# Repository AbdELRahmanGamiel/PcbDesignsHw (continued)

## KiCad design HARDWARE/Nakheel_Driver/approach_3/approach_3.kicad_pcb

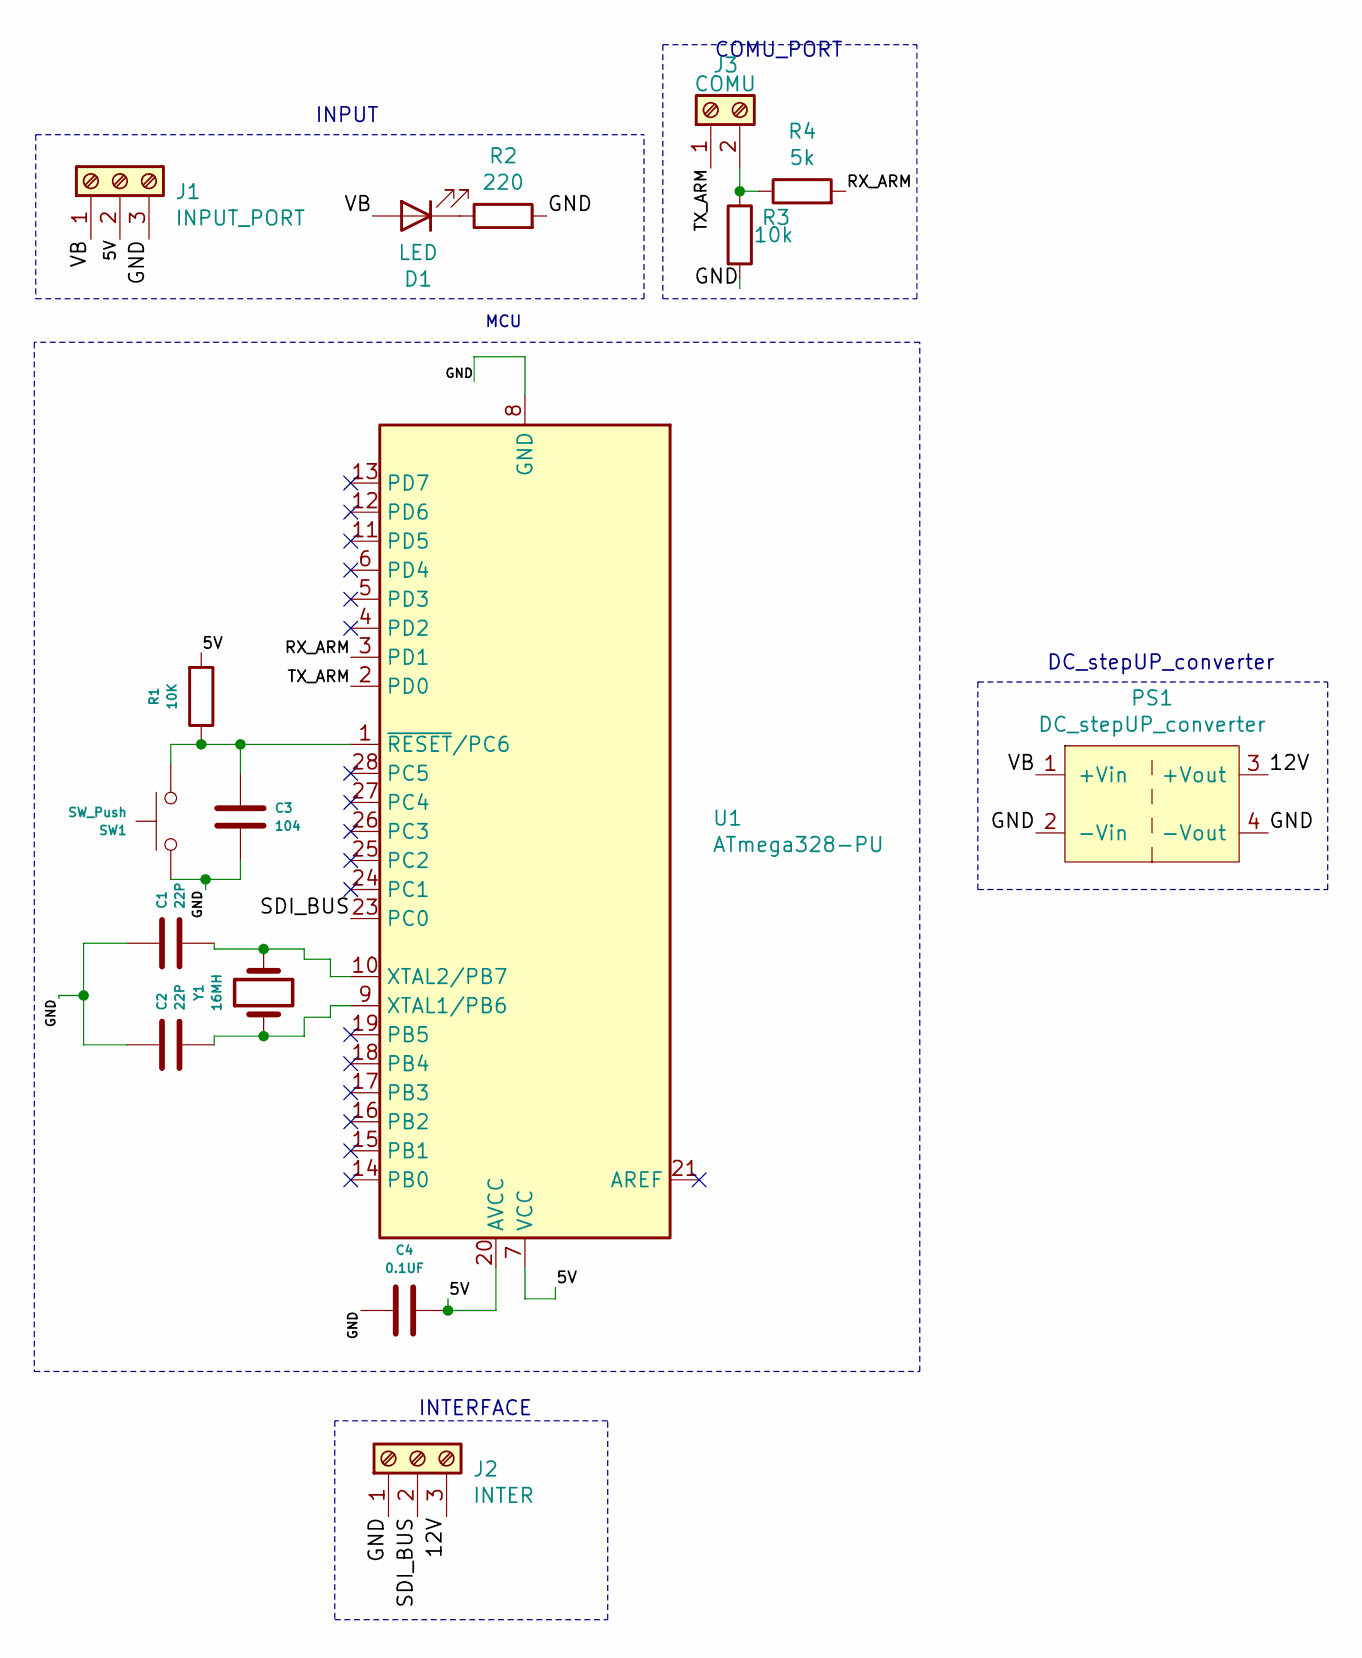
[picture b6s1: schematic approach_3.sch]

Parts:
C1, C2: 22P; C_Disc_D7.0mm_W2.5mm_P5.00mm
C3: 104; C_Disc_D7.0mm_W2.5mm_P5.00mm
C4: 0.1UF; C_Disc_D7.0mm_W2.5mm_P5.00mm
D1: LED; LED_D5.0mm
J1: INPUT_PORT; PhoenixContact_MSTBA_2,5_3-G-5,08_1x03_P5.08mm_Horizontal
J2: INTER; PhoenixContact_MSTBA_2,5_3-G-5,08_1x03_P5.08mm_Horizontal
J3: COMU; PhoenixContact_MSTBA_2,5_2-G-5,08_1x02_P5.08mm_Horizontal
PS1: DC_stepUP_converter
R1: 10K; R_Axial_DIN0207_L6.3mm_D2.5mm_P10.16mm_Horizontal
R2: 220; R_Axial_DIN0207_L6.3mm_D2.5mm_P10.16mm_Horizontal
R3: 10k; R_Axial_DIN0207_L6.3mm_D2.5mm_P10.16mm_Horizontal
R4: 5k; R_Axial_DIN0207_L6.3mm_D2.5mm_P10.16mm_Horizontal
SW1: SW_Push; SW_PUSH_6mm_H7.3mm
U1: ATmega328-PU; DIP-28_W7.62mm_Socket_LongPads
Y1: 16MH; Resonator-2Pin_W10.0mm_H5.0mm

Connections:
/5V: C4.1, J1.2, R1.2, U1.7 (VCC), U1.20 (AVCC)
/12V: J2.3, PS1.3 (+Vout)
/GND: C1.2, C2.2, C3.1, C4.2, J1.3, J2.1, PS1.2 (-Vin), PS1.4 (-Vout), R2.2, R3.2, SW1.1, U1.8 (GND), U1.22 (GND)
/RX_ARM: R4.2, U1.3 (PD1)
/SDI_BUS: J2.2, U1.23 (PC0)
/TX_ARM: J3.1, U1.2 (PD0)
/VB: D1.2 (A), J1.1, PS1.1 (+Vin)
unnamed: C1.1, U1.10 (XTAL2/PB7), Y1.2
unnamed: C2.1, U1.9 (XTAL1/PB6), Y1.1
unnamed: C3.2, R1.1, SW1.2, U1.1 (~RESET~/PC6)
unnamed: D1.1 (K), R2.1
unnamed: J3.2, R3.1, R4.1

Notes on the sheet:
INPUT
DC_stepUP_converter
INTERFACE
MCU
COMU_PORT

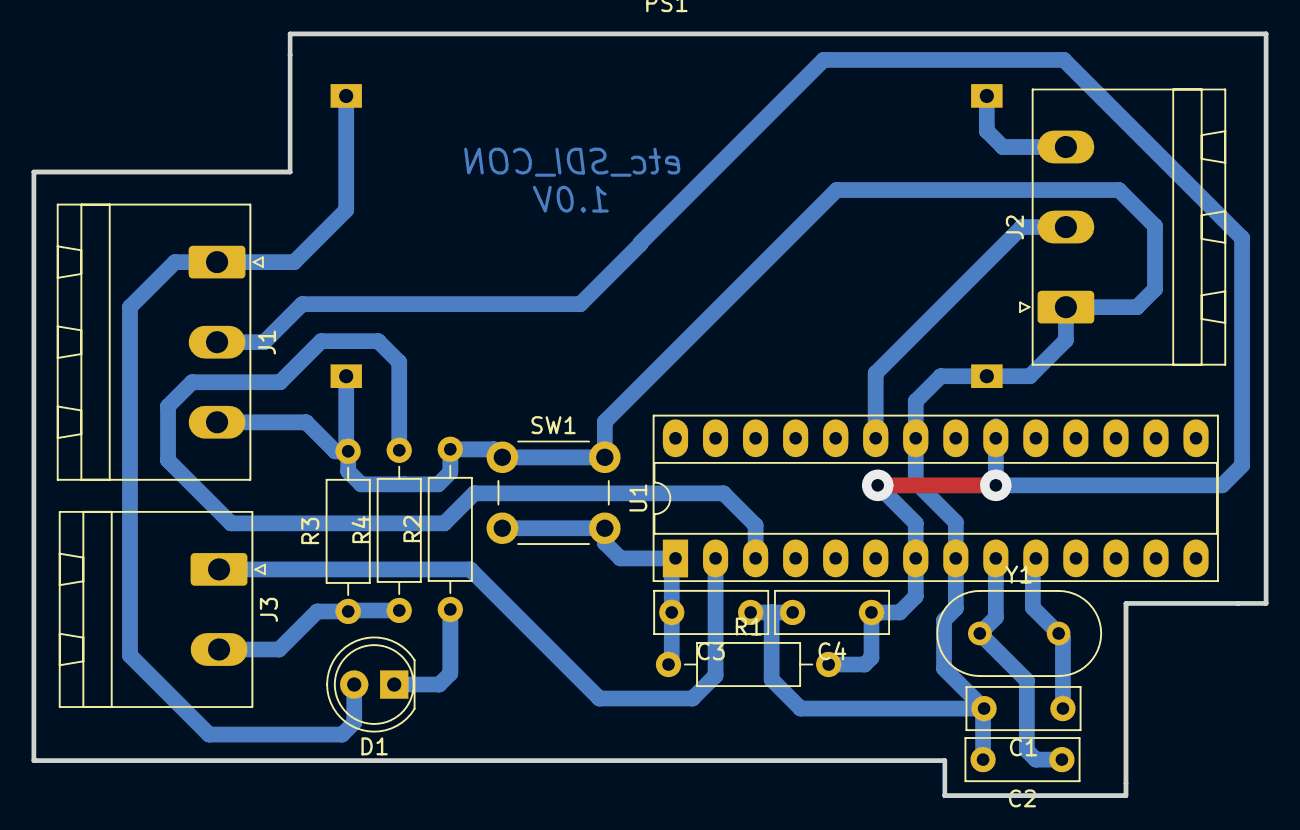
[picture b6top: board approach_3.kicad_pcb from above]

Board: 2 copper layers, 78.2 x 48.3 mm, 16 parts (0 on the bottom side), 12 nets.

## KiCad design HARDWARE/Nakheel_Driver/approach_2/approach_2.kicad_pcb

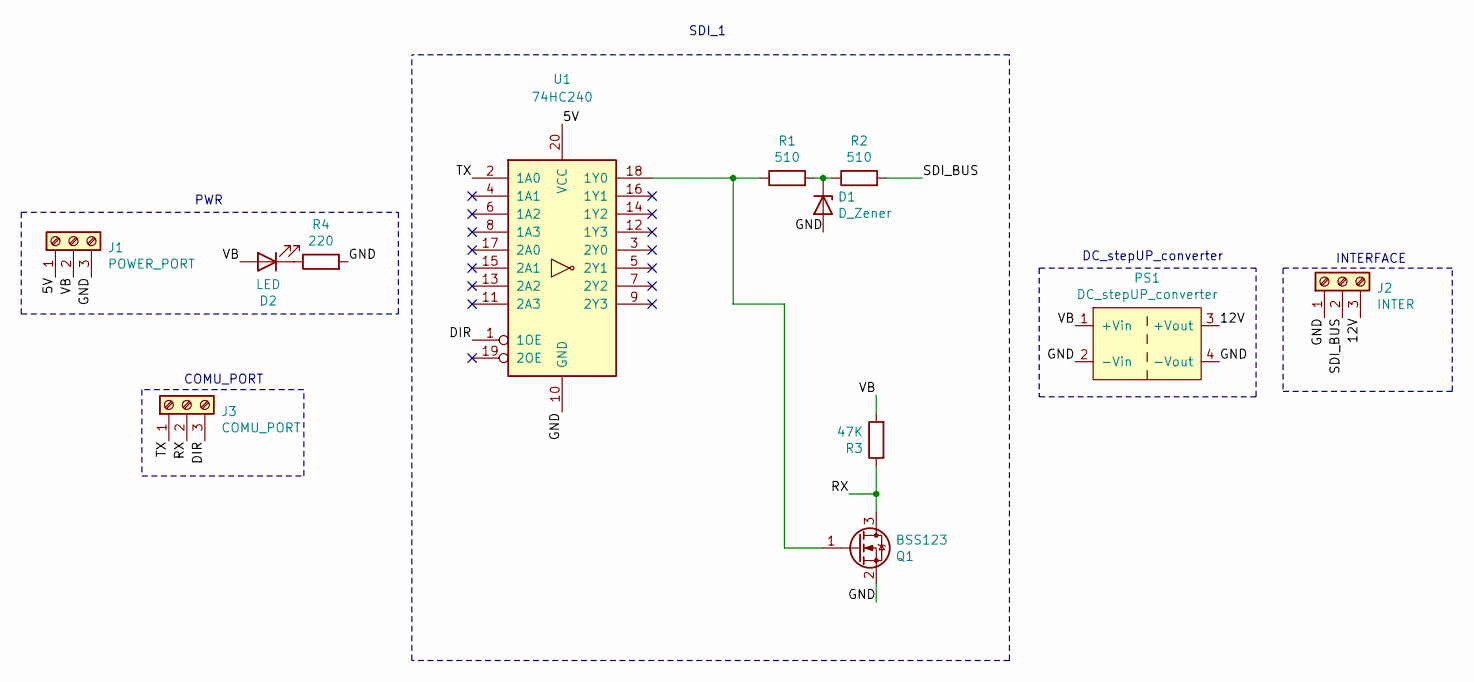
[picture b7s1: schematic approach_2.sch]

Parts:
D1: D_Zener; D_A-405_P7.62mm_Horizontal
D2: LED; LED_D5.0mm
J1: POWER_PORT; PhoenixContact_MSTBA_2,5_3-G-5,08_1x03_P5.08mm_Horizontal
J2: INTER; PhoenixContact_MSTBA_2,5_3-G-5,08_1x03_P5.08mm_Horizontal
J3: COMU_PORT; PhoenixContact_MSTBA_2,5_3-G-5,08_1x03_P5.08mm_Horizontal
PS1: DC_stepUP_converter
Q1: BSS123; TO-92L_Wide
R1, R2: 510; R_Axial_DIN0207_L6.3mm_D2.5mm_P10.16mm_Horizontal
R3: 47K; R_Axial_DIN0207_L6.3mm_D2.5mm_P10.16mm_Horizontal
R4: 220; R_Axial_DIN0207_L6.3mm_D2.5mm_P10.16mm_Horizontal
U1: 74HC240; DIP-20_W7.62mm_Socket_LongPads

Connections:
/5V: J1.1, U1.20 (VCC)
/12V: J2.3, PS1.3 (+Vout)
/DIR: J3.3, U1.1 (1OE)
/GND: D1.2 (A), J1.3, J2.1, PS1.2 (-Vin), PS1.4 (-Vout), Q1.2 (S), R4.2, U1.10 (GND)
/RX: J3.2, Q1.3 (D), R3.1
/SDI_BUS: J2.2, R2.2
/TX: J3.1, U1.2 (1A0)
/VB: D2.2 (A), J1.2, PS1.1 (+Vin), R3.2
unnamed: D1.1 (K), R1.2, R2.1
unnamed: D2.1 (K), R4.1
unnamed: Q1.1 (G), R1.1, U1.18 (1Y0)

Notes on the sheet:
SDI_1
PWR
DC_stepUP_converter
COMU_PORT
INTERFACE

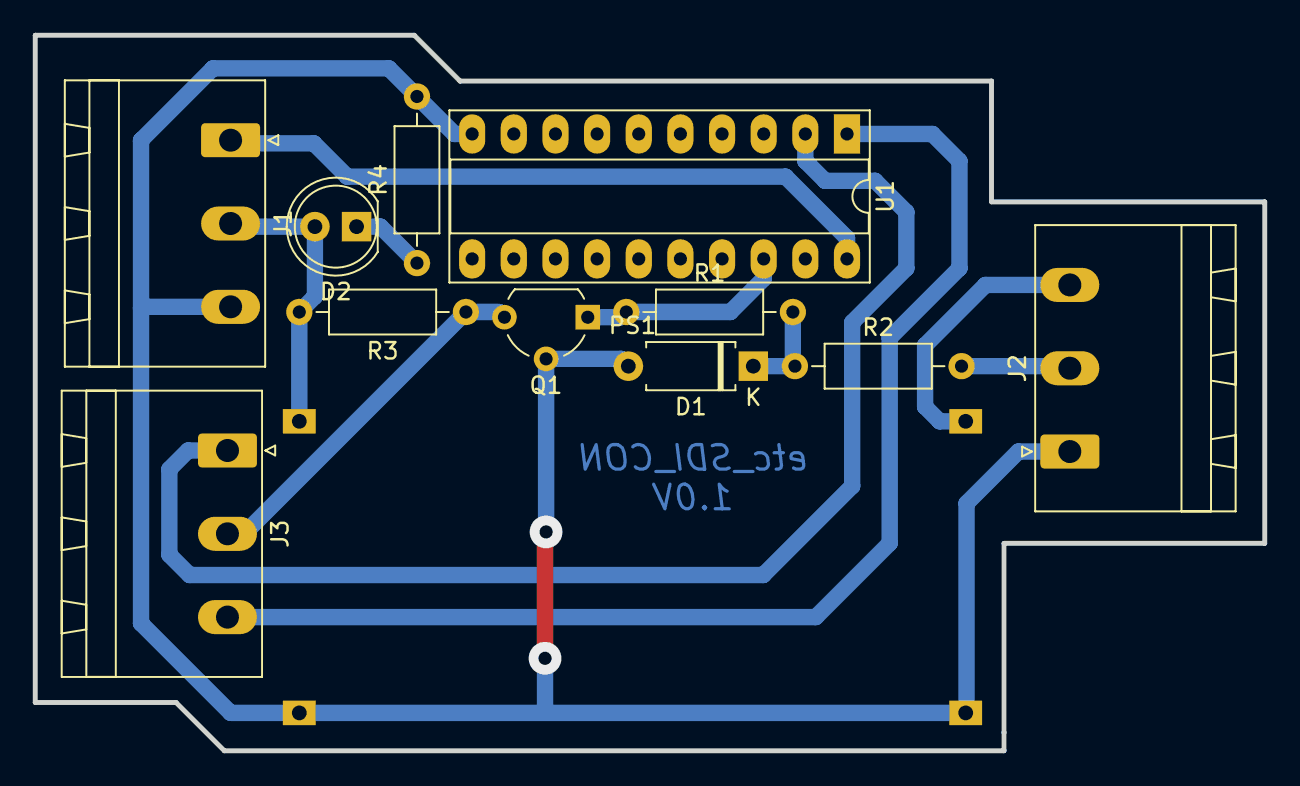
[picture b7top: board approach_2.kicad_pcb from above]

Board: 2 copper layers, 75.0 x 43.6 mm, 12 parts (0 on the bottom side), 11 nets.

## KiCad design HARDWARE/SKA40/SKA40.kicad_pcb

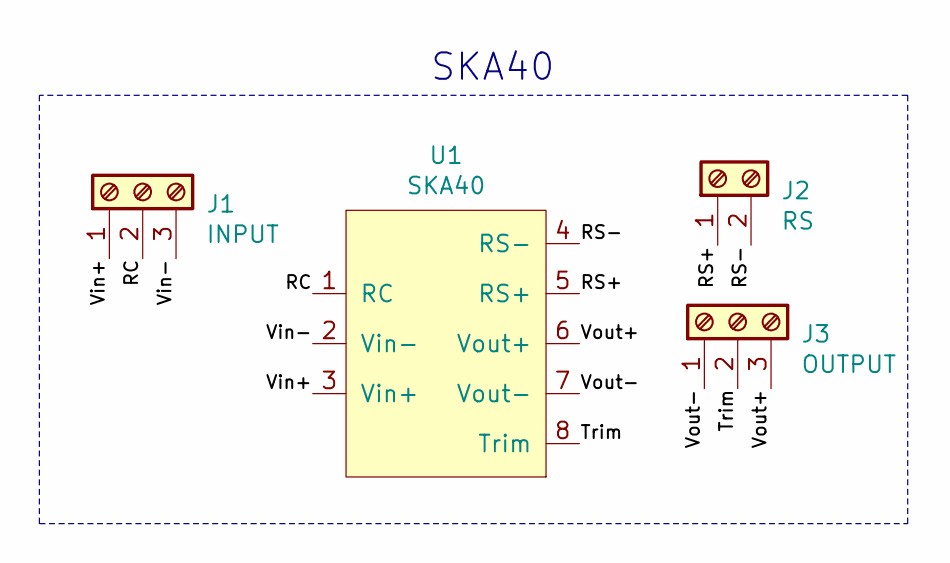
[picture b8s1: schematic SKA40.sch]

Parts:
J1: INPUT; PhoenixContact_MSTBA_2,5_3-G-5,08_1x03_P5.08mm_Horizontal
J2: RS; PhoenixContact_MSTBA_2,5_2-G-5,08_1x02_P5.08mm_Horizontal
J3: OUTPUT; PhoenixContact_MSTBA_2,5_3-G-5,08_1x03_P5.08mm_Horizontal
U1: SKA40

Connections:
/RC: J1.2, U1.1 (RC)
/RS+: J2.1, U1.5 (RS+)
/RS-: J2.2, U1.4 (RS-)
/Trim: J3.2, U1.8 (Trim)
/Vin+: J1.1, U1.3 (Vin+)
/Vin-: J1.3, U1.2 (Vin-)
/Vout+: J3.3, U1.6 (Vout+)
/Vout-: J3.1, U1.7 (Vout-)

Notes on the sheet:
SKA40

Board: 2 copper layers, 4 parts (0 on the bottom side), 8 nets, no tracks yet.

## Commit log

2024-07-24 Adding initial repo
2026-05-16 Add heater project and lamp design
2026-05-16 WIP: ModeeLamp PCB placement, heater project, Nakheel_Driver updates; ignore .history
2026-05-24 Fixing PCB review points and add interactive BOM
